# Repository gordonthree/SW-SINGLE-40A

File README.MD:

# Smart Switch Node
* Single BTS50010-1TAD Profet Smart Switch
* Heavy duty terminal block connectors for power in/out
* Pin-header connections for linking to a can bus control module
* Voltage divider for measuring supply voltage
<IMG src="https://github.com/gordonthree/SW-SINGLE-40A/blob/main/SW-SINGLE-40A.png?raw=true" width=480>

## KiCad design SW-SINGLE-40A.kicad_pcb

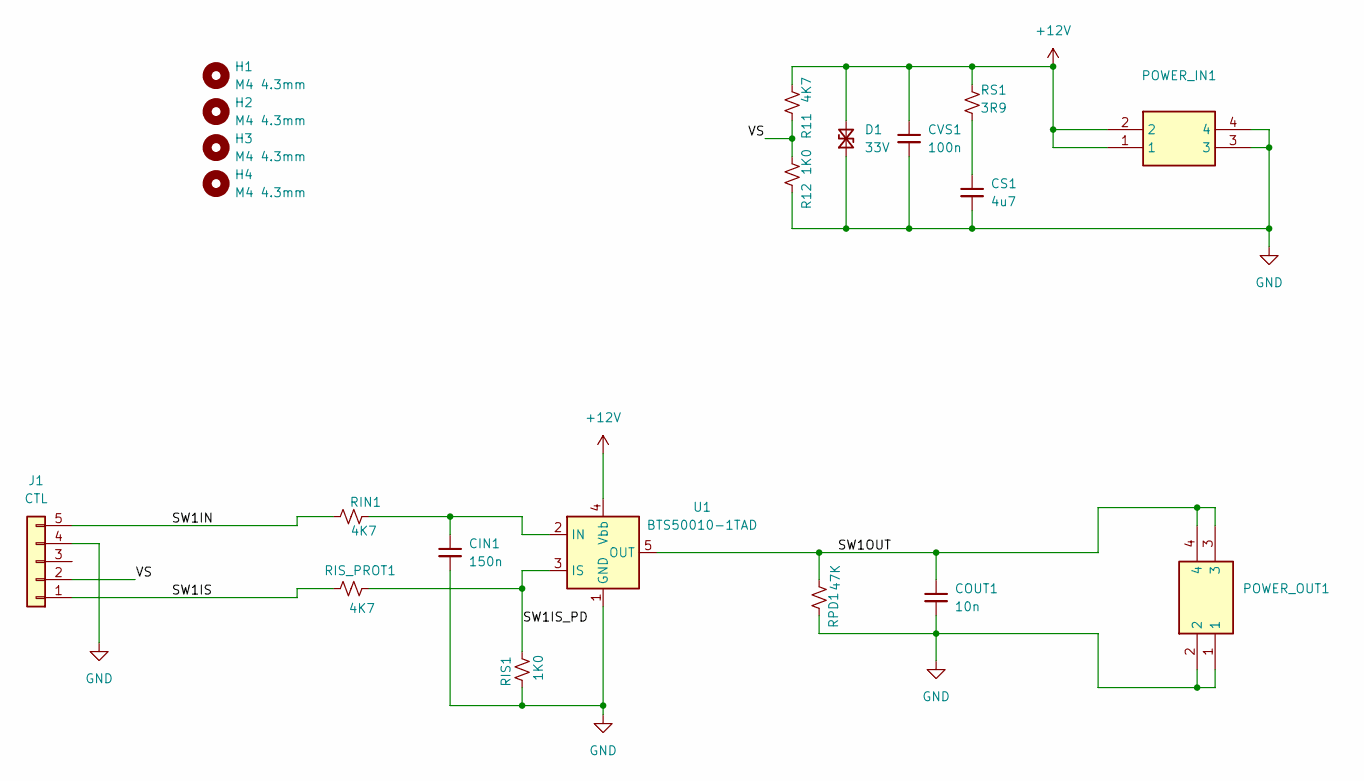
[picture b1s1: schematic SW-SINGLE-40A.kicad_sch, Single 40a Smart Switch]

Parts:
CIN1: 150n; C_0603_1608Metric_Pad1.08x0.95mm_HandSolder
COUT1: 10n; C_0603_1608Metric_Pad1.08x0.95mm_HandSolder
CS1: 4u7; C_0603_1608Metric_Pad1.08x0.95mm_HandSolder
CVS1: 100n; C_0603_1608Metric_Pad1.08x0.95mm_HandSolder
D1: 33V; D_SMA_Handsoldering
H1, H2, H3, H4: M4 4.3mm; MountingHole_4.3mm_M4
J1: CTL; PinHeader_1x05_P2.54mm_Horizontal
POWER_IN1: PWRIN; VP0265840000G; Mouser Part Number 649-VP02658400J0G
POWER_OUT1: SW OUT; VP0265840000G; Mouser Part Number 649-VP02658400J0G
R11: 4K7; R_Axial_DIN0207_L6.3mm_D2.5mm_P7.62mm_Horizontal
R12: 1K0; R_Axial_DIN0207_L6.3mm_D2.5mm_P7.62mm_Horizontal
RIN1: 4K7; R_0603_1608Metric_Pad0.98x0.95mm_HandSolder
RIS1: 1K0; R_0603_1608Metric_Pad0.98x0.95mm_HandSolder
RIS_PROT1: 4K7; R_0603_1608Metric_Pad0.98x0.95mm_HandSolder
RPD1: 47K; R_0603_1608Metric_Pad0.98x0.95mm_HandSolder
RS1: 3R9; R_0603_1608Metric_Pad0.98x0.95mm_HandSolder
U1: BTS50010-1TAD; TO-263-7_TabPin4

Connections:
+12V: CVS1.1, D1.2 (A2), POWER_IN1.1, POWER_IN1.2, R11.2, RS1.2, U1.4 (Vbb)
/SW1IN: J1.5, RIN1.1
/SW1IS: J1.1, RIS_PROT1.1
/SW1IS_PD: RIS1.2, RIS_PROT1.2, U1.3 (IS)
/SW1OUT: COUT1.1, POWER_OUT1.3, POWER_OUT1.4, RPD1.2, U1.5 (OUT), U1.6 (OUT), U1.7 (OUT)
/VS: J1.2, R11.1, R12.2
GND: CIN1.2, COUT1.2, CS1.2, CVS1.2, D1.1 (A1), J1.4, POWER_IN1.3, POWER_IN1.4, POWER_OUT1.1, POWER_OUT1.2, R12.1, RIS1.1, RPD1.1, U1.1 (GND)
unnamed: CS1.1, RS1.1
unnamed: CIN1.1, RIN1.2, U1.2 (IN)

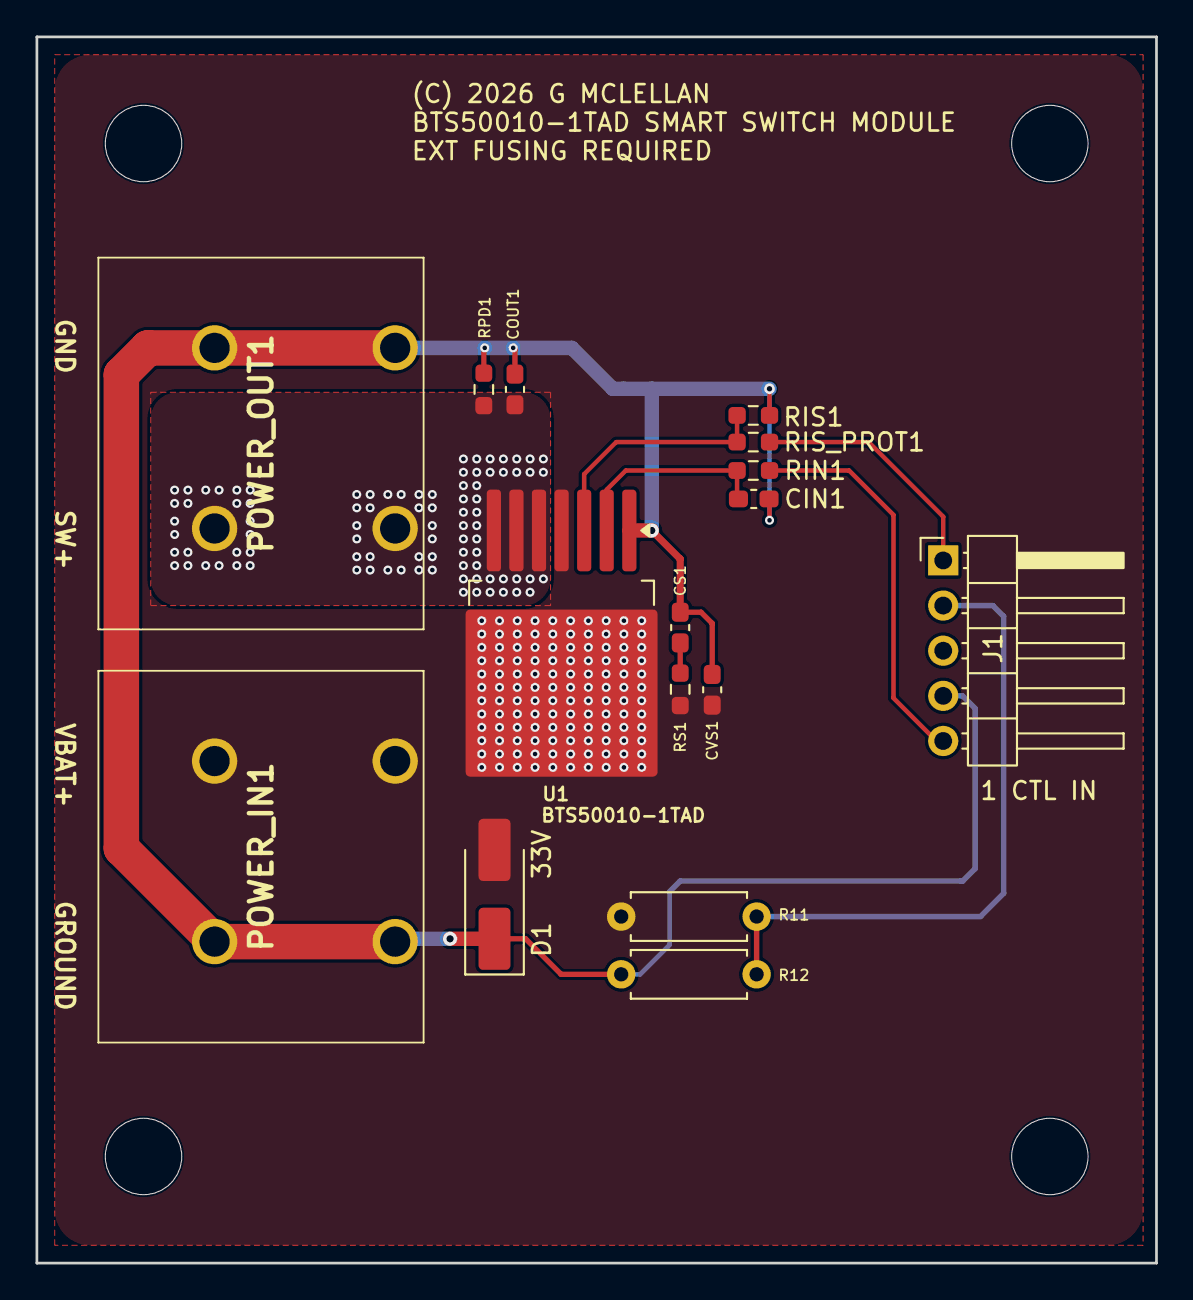
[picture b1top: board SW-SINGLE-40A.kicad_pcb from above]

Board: 2 copper layers, 63.0 x 69.0 mm, 20 parts (0 on the bottom side), 9 nets.

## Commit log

2026-01-17 added 3d rendering
2026-01-17 added 3d rendering to readme
2026-01-17 layout and silkscreen tweaks

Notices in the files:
SW-SINGLE-40A.kicad_pcb:
(C) 2026 G MCLELLAN
